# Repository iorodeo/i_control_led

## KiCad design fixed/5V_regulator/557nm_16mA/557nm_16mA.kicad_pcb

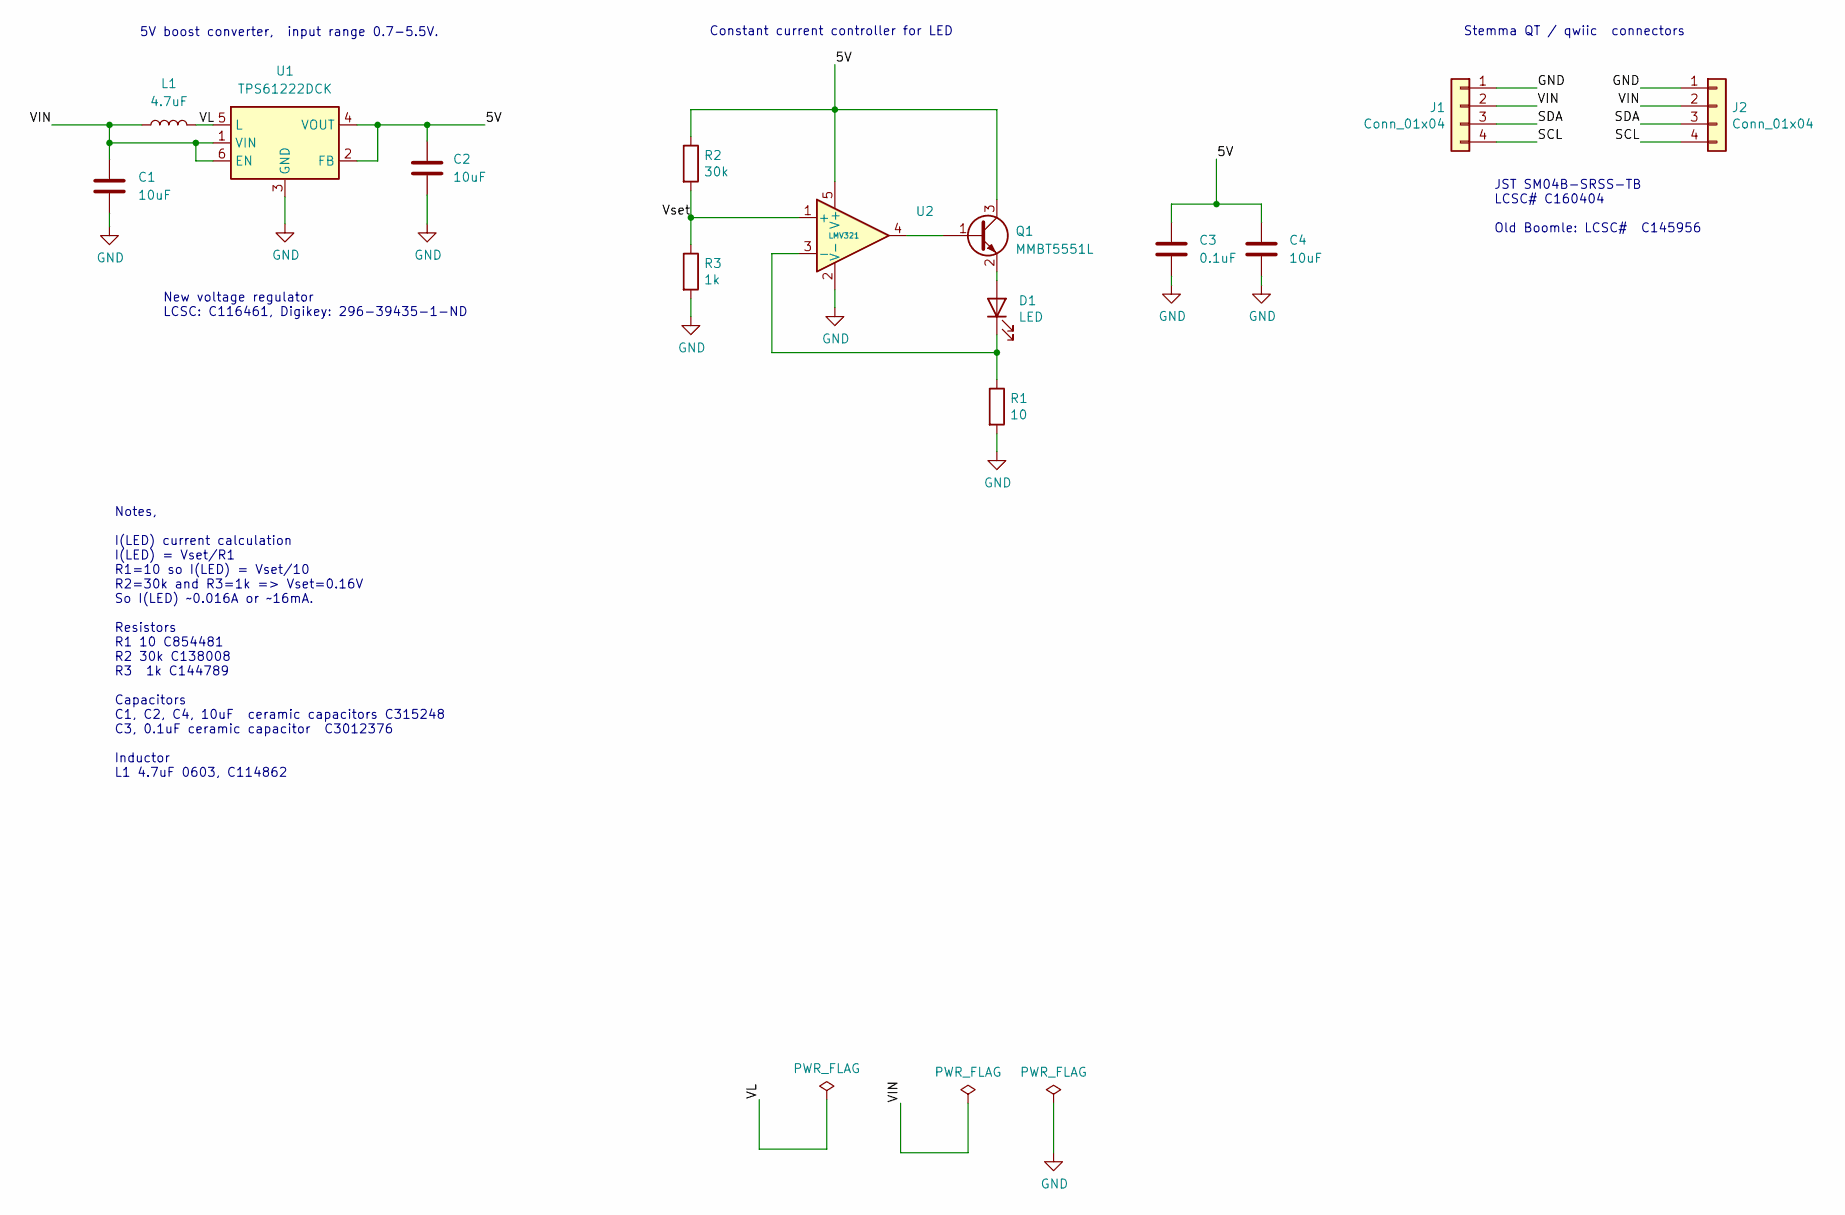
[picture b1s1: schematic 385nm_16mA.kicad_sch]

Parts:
C1, C2, C4: 10uF; C_0402_1005Metric
C3: 0.1uF; C_0402_1005Metric
D1: LED; LED_0805_2012Metric
J1, J2: Conn_01x04; JST_SH_SM04B-SRSS-TB_1x04-1MP_P1.00mm_Horizontal
L1: 4.7uF; L_0603_1608Metric
Q1: MMBT5551L; SOT-23
R1: 10; R_0402_1005Metric
R2: 30k; R_0402_1005Metric
R3: 1k; R_0402_1005Metric
U1: TPS61222DCK; SOT-363_SC-70-6
U2: LMV321; SOT-23-5

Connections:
/5V: C2.2, C3.1, C4.1, Q1.3 (C), R2.1, U1.2 (FB), U1.4 (VOUT), U2.5 (V+)
/SCL: J1.4, J2.4
/SDA: J1.3, J2.3
/VIN: C1.2, J1.2, J2.2, L1.1, U1.1 (VIN), U1.6 (EN)
/VL: L1.2, U1.5 (L)
/Vset: R2.2, R3.1, U2.1 (+)
GND: C1.1, C2.1, C3.2, C4.2, J1.1, J2.1, R1.2, R3.2, U1.3 (GND), U2.2 (V-)
unnamed: D1.2 (A), Q1.2 (E)
unnamed: D1.1 (K), R1.1, U2.3 (-)
unnamed: Q1.1 (B), U2.4

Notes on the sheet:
JST SM04B-SRSS-TB LCSC# C160404 Old Boomle: LCSC# C145956
Stemma QT / qwiic connectors
New voltage regulator LCSC: C116461, Digikey: 296-39435-1-ND
Constant current controller for LED
5V boost converter, input range 0.7-5.5V.
Notes, I(LED) current calculation I(LED) = Vset/R1 R1=10 so I(LED) = Vset/10 R2=30k and R3=1k => Vset=0.16V So I(LED) ~0.016A or ~16mA. Resistors R1 10 C854481 R2 30k C138008 R3 1k C144789 Capacitors C1, C2, C4, 10uF ceramic capacitors C315248 C3, 0.1uF ceramic capacitor C3012376 Inductor L1 4.7uF 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

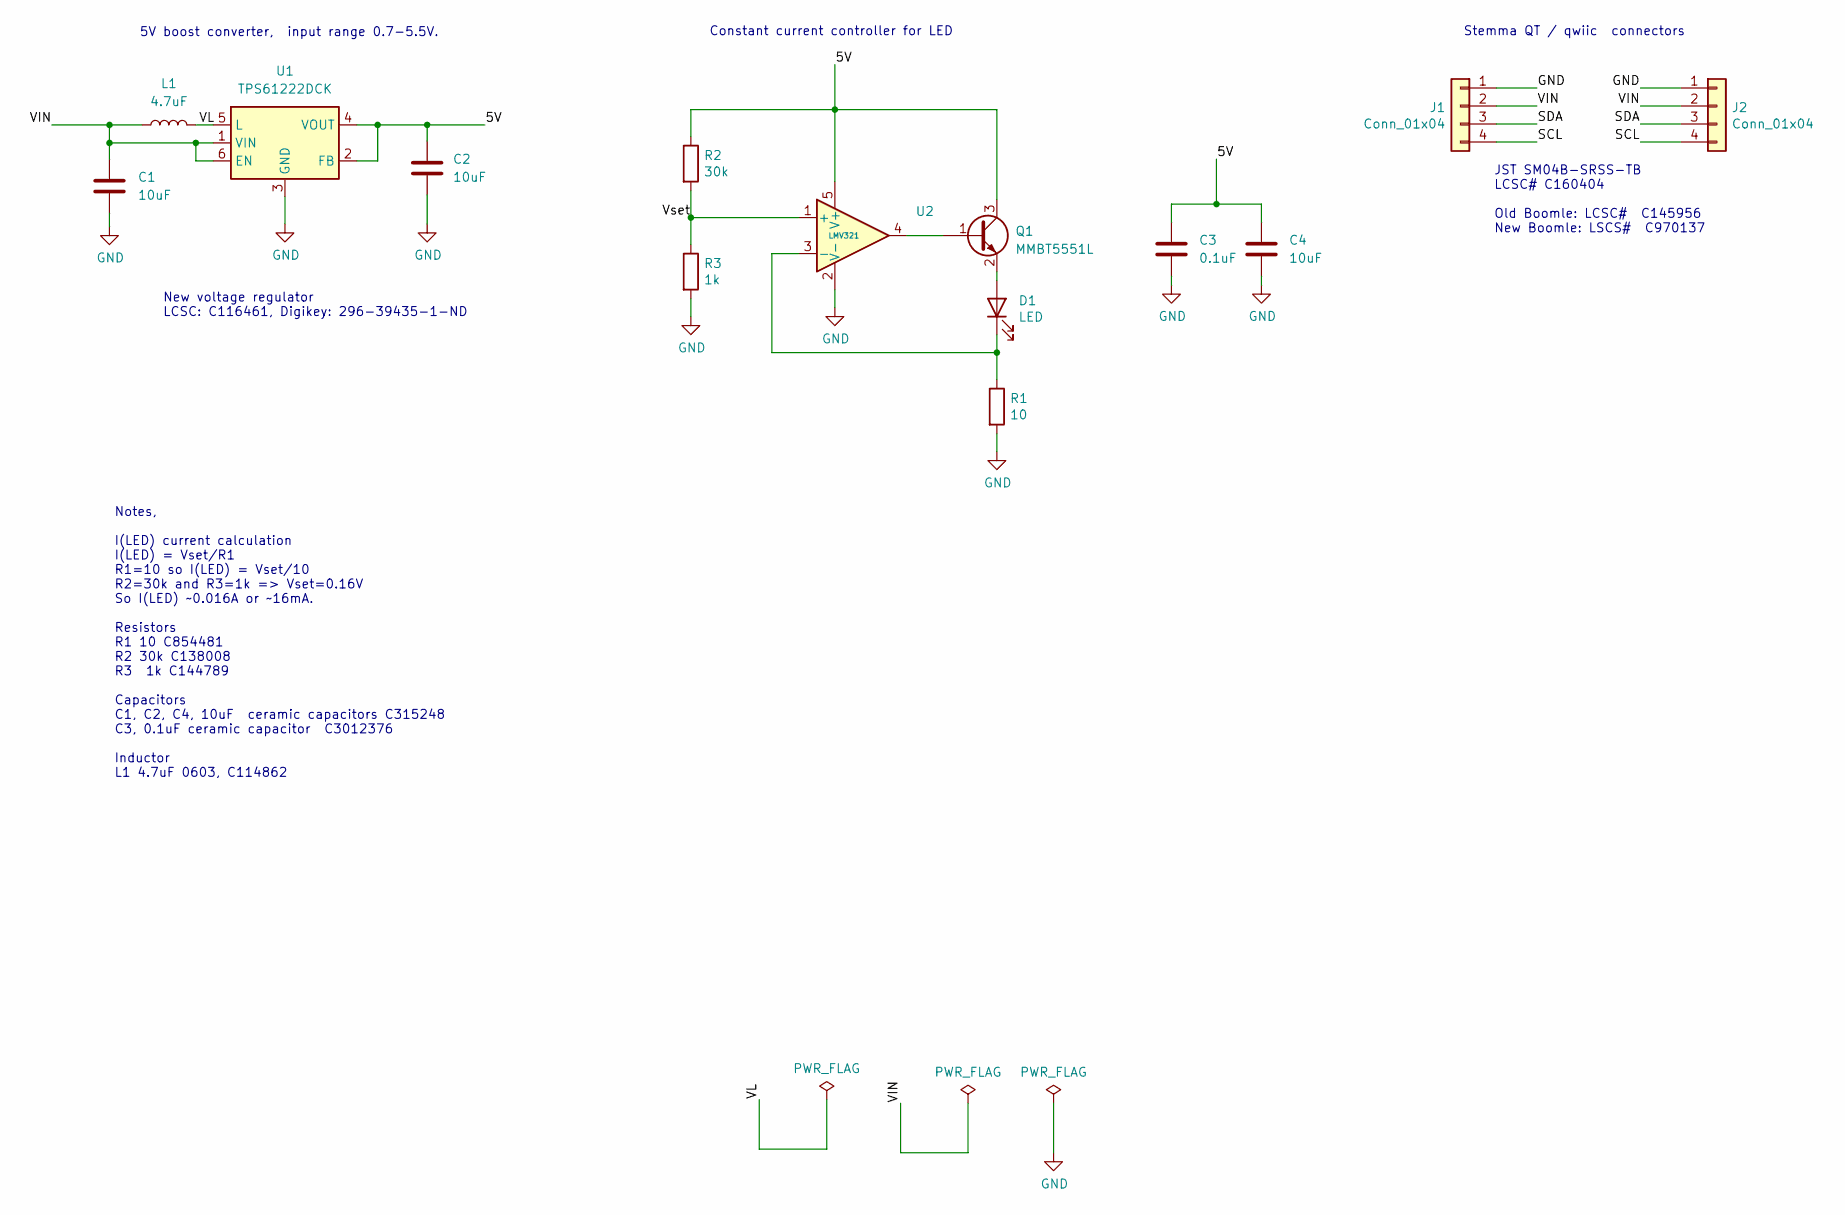
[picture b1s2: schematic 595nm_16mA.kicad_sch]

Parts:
C1, C2, C4: 10uF; C_0402_1005Metric
C3: 0.1uF; C_0402_1005Metric
D1: LED; LED_0603_1608Metric
J1, J2: Conn_01x04; JST_SH_SM04B-SRSS-TB_1x04-1MP_P1.00mm_Horizontal
L1: 4.7uF; L_0603_1608Metric
Q1: MMBT5551L; SOT-23
R1: 10; R_0402_1005Metric
R2: 30k; R_0402_1005Metric
R3: 1k; R_0402_1005Metric
U1: TPS61222DCK; SOT-363_SC-70-6
U2: LMV321; SOT-23-5

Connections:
/5V: C2.2, C3.1, C4.1, Q1.3 (C), R2.1, U1.2 (FB), U1.4 (VOUT), U2.5 (V+)
/SCL: J1.4, J2.4
/SDA: J1.3, J2.3
/VIN: C1.2, J1.2, J2.2, L1.1, U1.1 (VIN), U1.6 (EN)
/VL: L1.2, U1.5 (L)
/Vset: R2.2, R3.1, U2.1 (+)
GND: C1.1, C2.1, C3.2, C4.2, J1.1, J2.1, R1.2, R3.2, U1.3 (GND), U2.2 (V-)
unnamed: D1.2 (A), Q1.2 (E)
unnamed: D1.1 (K), R1.1, U2.3 (-)
unnamed: Q1.1 (B), U2.4

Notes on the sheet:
JST SM04B-SRSS-TB LCSC# C160404 Old Boomle: LCSC# C145956 New Boomle: LSCS# C970137
Stemma QT / qwiic connectors
New voltage regulator LCSC: C116461, Digikey: 296-39435-1-ND
Constant current controller for LED
5V boost converter, input range 0.7-5.5V.
Notes, I(LED) current calculation I(LED) = Vset/R1 R1=10 so I(LED) = Vset/10 R2=30k and R3=1k => Vset=0.16V So I(LED) ~0.016A or ~16mA. Resistors R1 10 C854481 R2 30k C138008 R3 1k C144789 Capacitors C1, C2, C4, 10uF ceramic capacitors C315248 C3, 0.1uF ceramic capacitor C3012376 Inductor L1 4.7uF 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

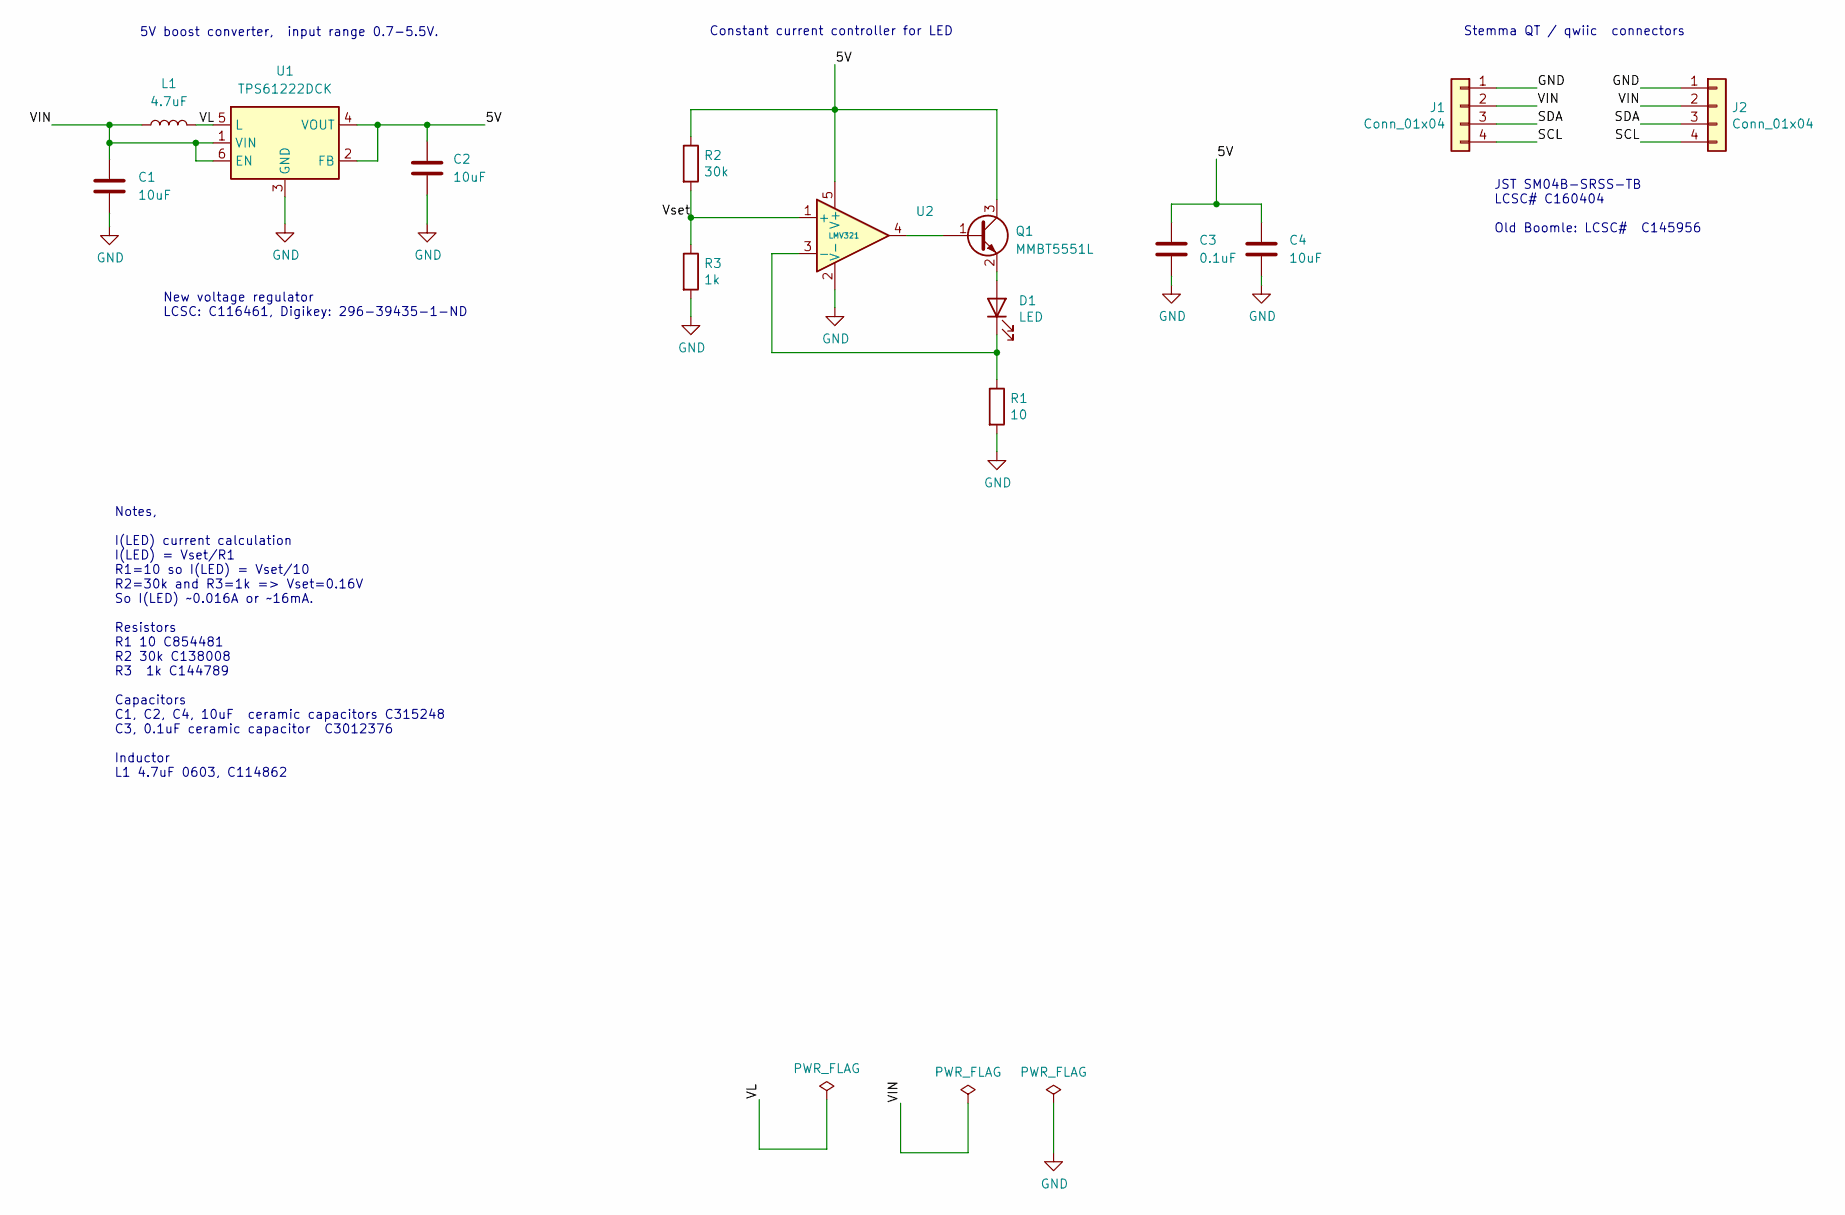
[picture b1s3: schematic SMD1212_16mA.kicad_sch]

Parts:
C1, C2, C4: 10uF; C_0402_1005Metric
C3: 0.1uF; C_0402_1005Metric
D1: LED; SMD1212
J1, J2: Conn_01x04; JST_SH_SM04B-SRSS-TB_1x04-1MP_P1.00mm_Horizontal
L1: 4.7uF; L_0603_1608Metric
Q1: MMBT5551L; SOT-23
R1: 10; R_0402_1005Metric
R2: 30k; R_0402_1005Metric
R3: 1k; R_0402_1005Metric
U1: TPS61222DCK; SOT-363_SC-70-6
U2: LMV321; SOT-23-5

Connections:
/5V: C2.2, C3.1, C4.1, Q1.3 (C), R2.1, U1.2 (FB), U1.4 (VOUT), U2.5 (V+)
/SCL: J1.4, J2.4
/SDA: J1.3, J2.3
/VIN: C1.2, J1.2, J2.2, L1.1, U1.1 (VIN), U1.6 (EN)
/VL: L1.2, U1.5 (L)
/Vset: R2.2, R3.1, U2.1 (+)
GND: C1.1, C2.1, C3.2, C4.2, J1.1, J2.1, R1.2, R3.2, U1.3 (GND), U2.2 (V-)
unnamed: D1.2 (A), Q1.2 (E)
unnamed: D1.1 (K), R1.1, U2.3 (-)
unnamed: Q1.1 (B), U2.4

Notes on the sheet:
JST SM04B-SRSS-TB LCSC# C160404 Old Boomle: LCSC# C145956
Stemma QT / qwiic connectors
New voltage regulator LCSC: C116461, Digikey: 296-39435-1-ND
Constant current controller for LED
5V boost converter, input range 0.7-5.5V.
Notes, I(LED) current calculation I(LED) = Vset/R1 R1=10 so I(LED) = Vset/10 R2=30k and R3=1k => Vset=0.16V So I(LED) ~0.016A or ~16mA. Resistors R1 10 C854481 R2 30k C138008 R3 1k C144789 Capacitors C1, C2, C4, 10uF ceramic capacitors C315248 C3, 0.1uF ceramic capacitor C3012376 Inductor L1 4.7uF 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

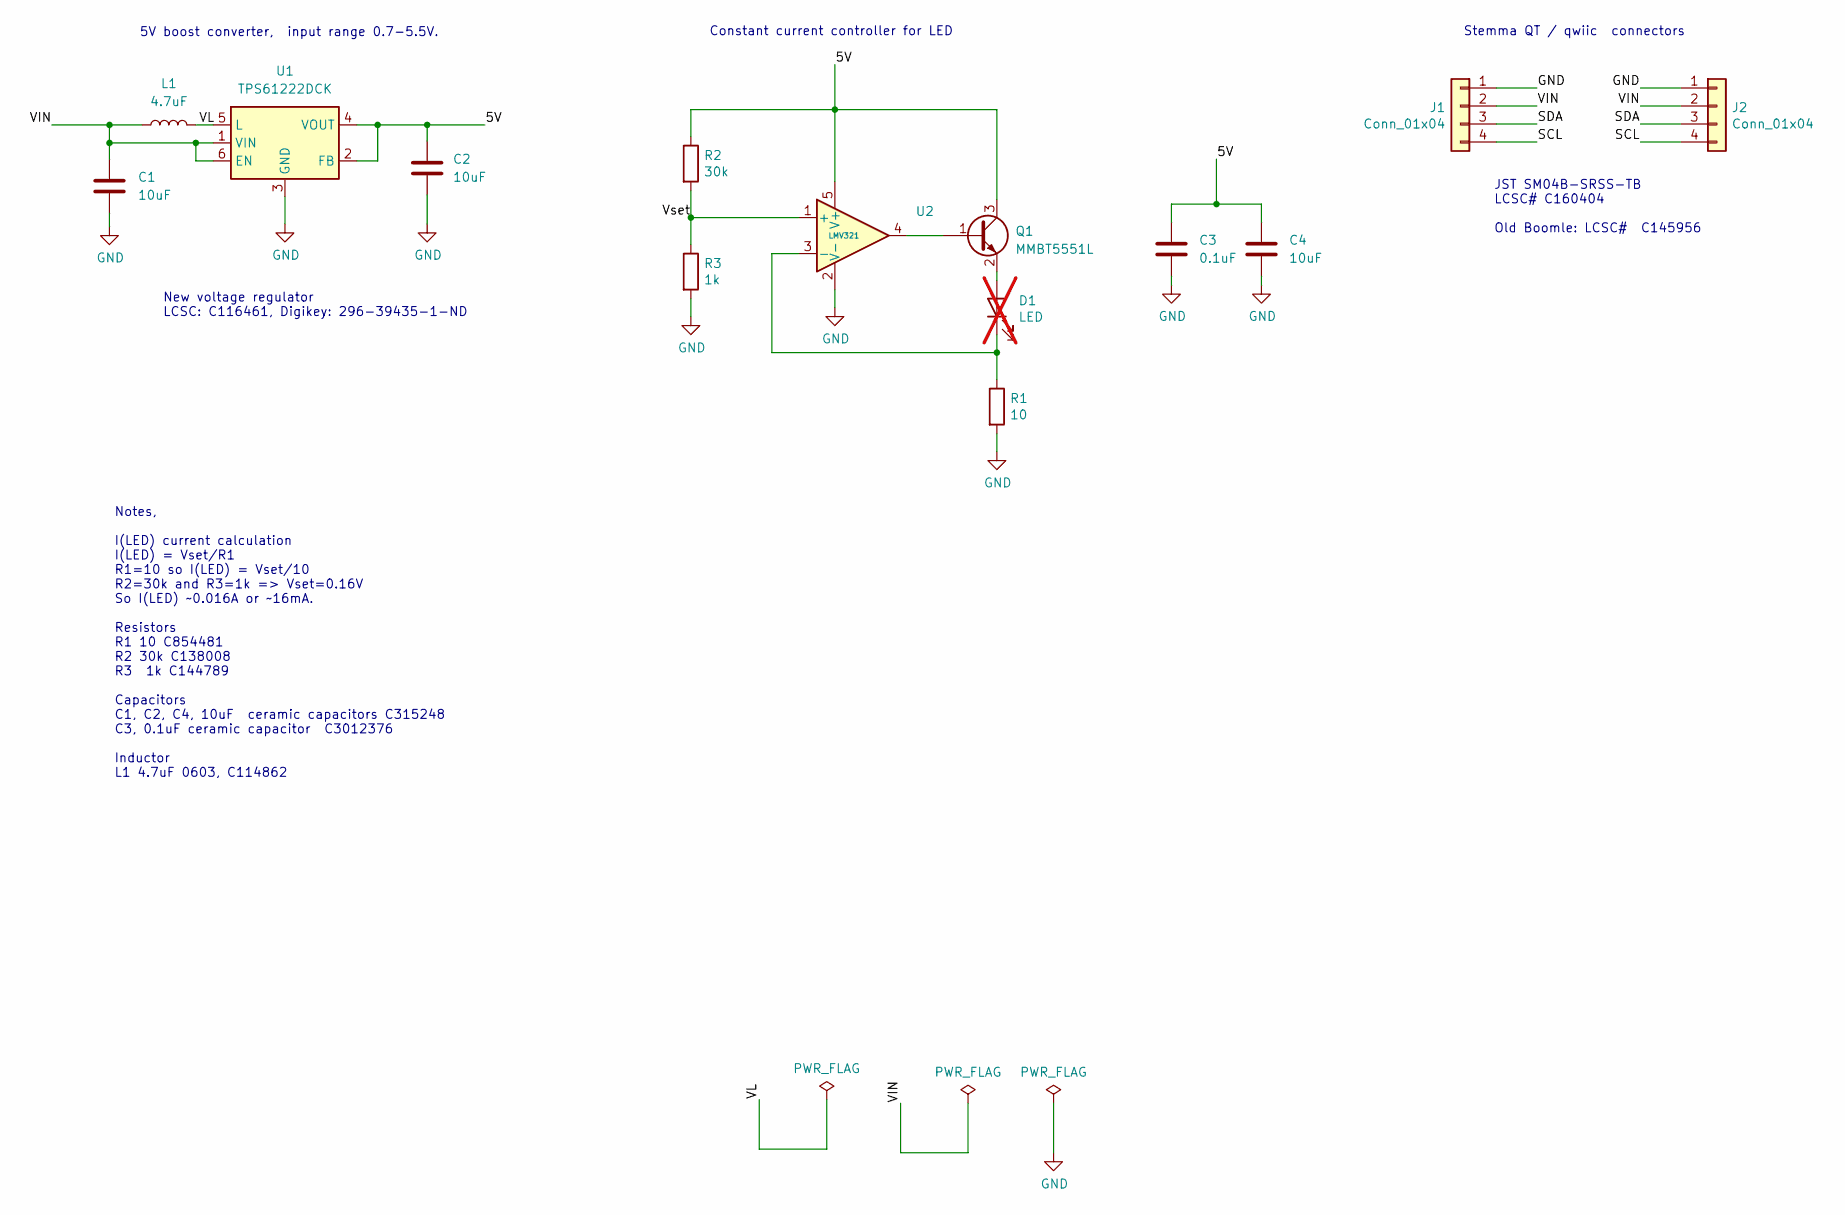
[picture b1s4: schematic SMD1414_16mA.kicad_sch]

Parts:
C1, C2, C4: 10uF; C_0402_1005Metric; LCSC Part # C315248
C3: 0.1uF; C_0402_1005Metric; LCSC Part # C1525
D1: LED; LED_1414; not fitted
J1, J2: Conn_01x04; JST_SH_SM04B-SRSS-TB_1x04-1MP_P1.00mm_Horizontal; LCSC Part # C160404
L1: 4.7uF; L_0603_1608Metric; LCSC Part # C114862
Q1: MMBT5551L; SOT-23; LCSC Part # C41095
R1: 10; R_0402_1005Metric; LCSC Part # C413044
R2: 30k; R_0402_1005Metric; LCSC Part # C138008
R3: 1k; R_0402_1005Metric; LCSC Part # C144789
U1: TPS61222DCK; SOT-363_SC-70-6; LCSC Part # C116461
U2: LMV321; SOT-23-5; LCSC Part # C7972

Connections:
/5V: C2.2, C3.1, C4.1, Q1.3 (C), R2.1, U1.2 (FB), U1.4 (VOUT), U2.5 (V+)
/SCL: J1.4, J2.4
/SDA: J1.3, J2.3
/VIN: C1.2, J1.2, J2.2, L1.1, U1.1 (VIN), U1.6 (EN)
/VL: L1.2, U1.5 (L)
/Vset: R2.2, R3.1, U2.1 (+)
GND: C1.1, C2.1, C3.2, C4.2, J1.1, J2.1, R1.2, R3.2, U1.3 (GND), U2.2 (V-)
unnamed: D1.2 (A), Q1.2 (E)
unnamed: D1.1 (K), R1.1, U2.3 (-)
unnamed: Q1.1 (B), U2.4

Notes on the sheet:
JST SM04B-SRSS-TB LCSC# C160404 Old Boomle: LCSC# C145956
Stemma QT / qwiic connectors
New voltage regulator LCSC: C116461, Digikey: 296-39435-1-ND
Constant current controller for LED
5V boost converter, input range 0.7-5.5V.
Notes, I(LED) current calculation I(LED) = Vset/R1 R1=10 so I(LED) = Vset/10 R2=30k and R3=1k => Vset=0.16V So I(LED) ~0.016A or ~16mA. Resistors R1 10 C854481 R2 30k C138008 R3 1k C144789 Capacitors C1, C2, C4, 10uF ceramic capacitors C315248 C3, 0.1uF ceramic capacitor C3012376 Inductor L1 4.7uF 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

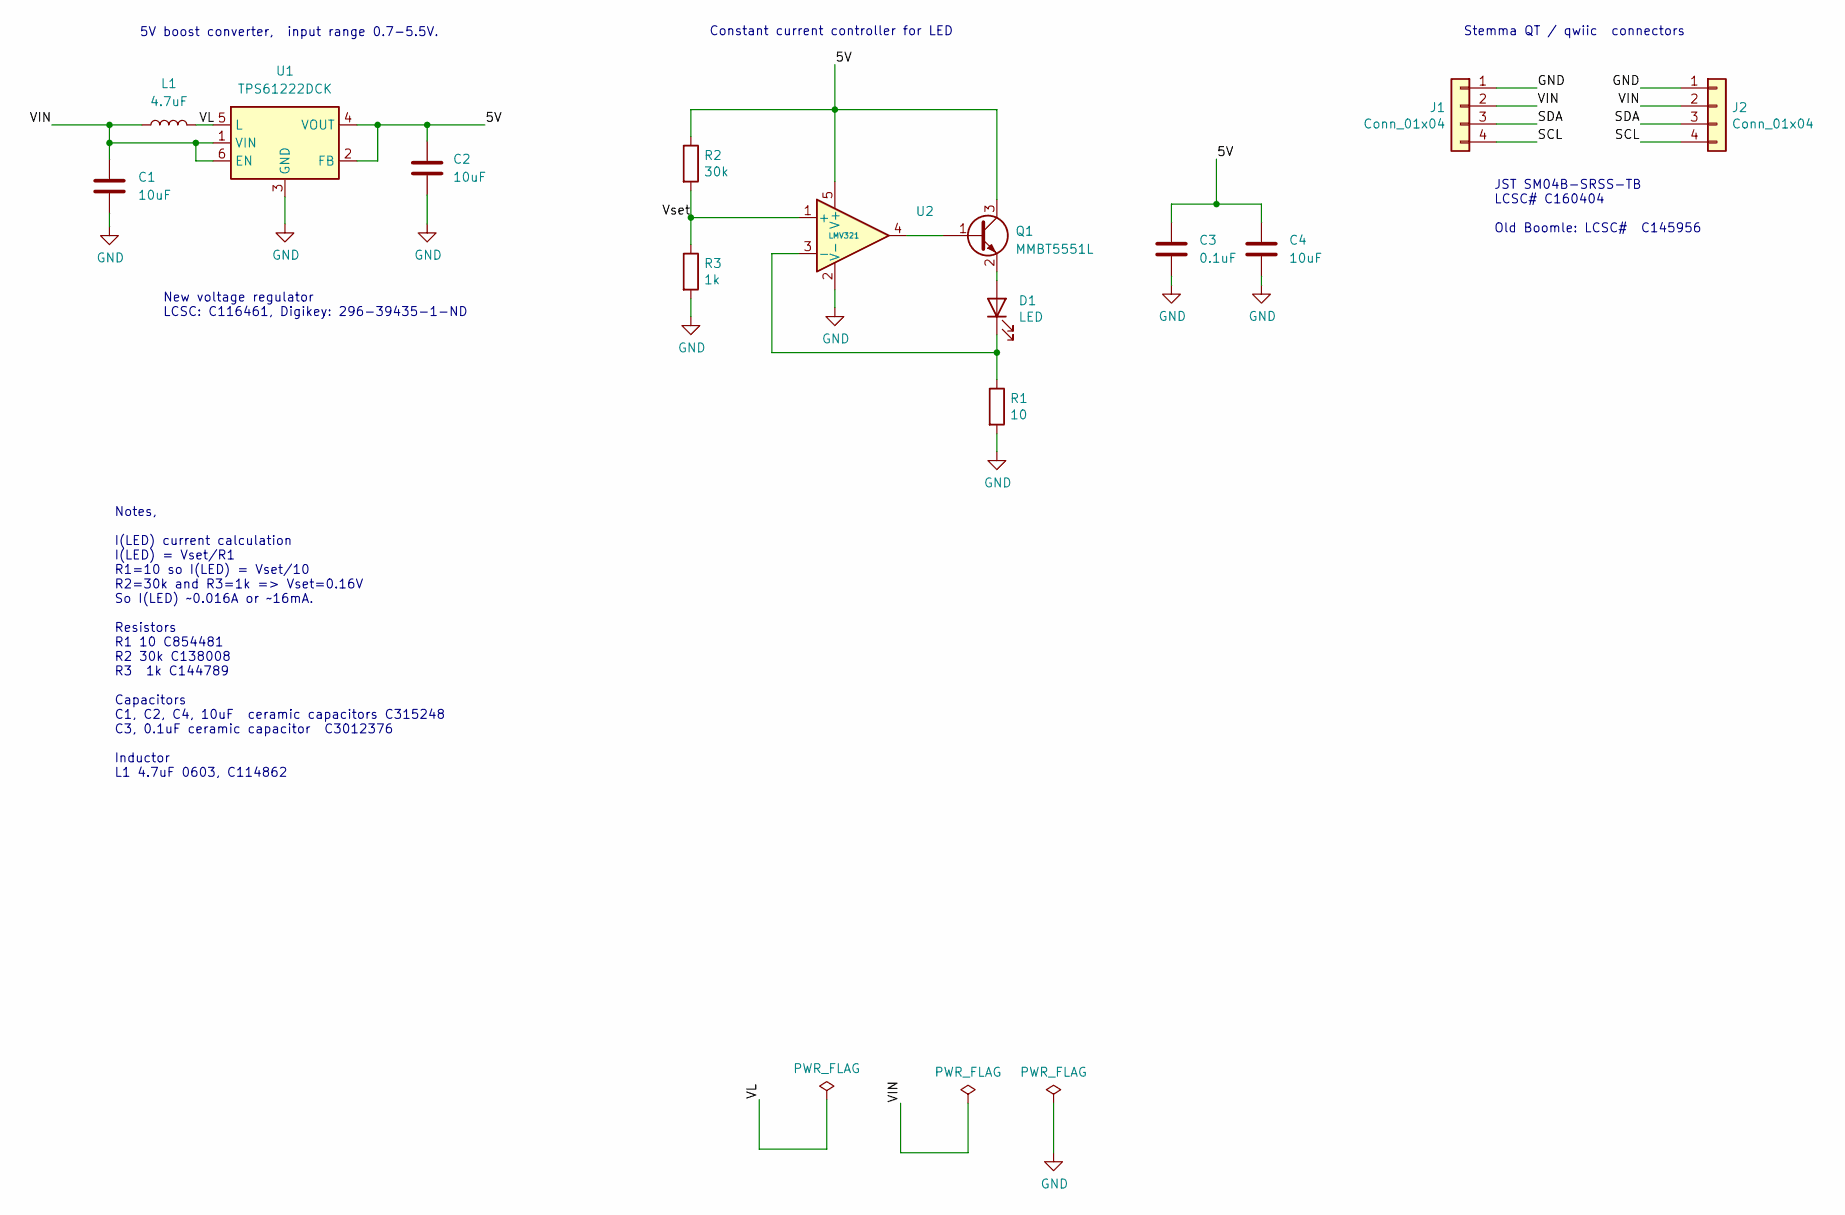
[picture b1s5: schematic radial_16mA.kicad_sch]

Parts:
C1, C2, C4: 10uF; C_0402_1005Metric
C3: 0.1uF; C_0402_1005Metric
D1: LED; LED_D3.0mm
J1, J2: Conn_01x04; JST_SH_SM04B-SRSS-TB_1x04-1MP_P1.00mm_Horizontal
L1: 4.7uF; L_0603_1608Metric
Q1: MMBT5551L; SOT-23
R1: 10; R_0402_1005Metric
R2: 30k; R_0402_1005Metric
R3: 1k; R_0402_1005Metric
U1: TPS61222DCK; SOT-363_SC-70-6
U2: LMV321; SOT-23-5

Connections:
/5V: C2.2, C3.1, C4.1, Q1.3 (C), R2.1, U1.2 (FB), U1.4 (VOUT), U2.5 (V+)
/SCL: J1.4, J2.4
/SDA: J1.3, J2.3
/VIN: C1.2, J1.2, J2.2, L1.1, U1.1 (VIN), U1.6 (EN)
/VL: L1.2, U1.5 (L)
/Vset: R2.2, R3.1, U2.1 (+)
GND: C1.1, C2.1, C3.2, C4.2, J1.1, J2.1, R1.2, R3.2, U1.3 (GND), U2.2 (V-)
unnamed: D1.2 (A), Q1.2 (E)
unnamed: D1.1 (K), R1.1, U2.3 (-)
unnamed: Q1.1 (B), U2.4

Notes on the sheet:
JST SM04B-SRSS-TB LCSC# C160404 Old Boomle: LCSC# C145956
Stemma QT / qwiic connectors
New voltage regulator LCSC: C116461, Digikey: 296-39435-1-ND
Constant current controller for LED
5V boost converter, input range 0.7-5.5V.
Notes, I(LED) current calculation I(LED) = Vset/R1 R1=10 so I(LED) = Vset/10 R2=30k and R3=1k => Vset=0.16V So I(LED) ~0.016A or ~16mA. Resistors R1 10 C854481 R2 30k C138008 R3 1k C144789 Capacitors C1, C2, C4, 10uF ceramic capacitors C315248 C3, 0.1uF ceramic capacitor C3012376 Inductor L1 4.7uF 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

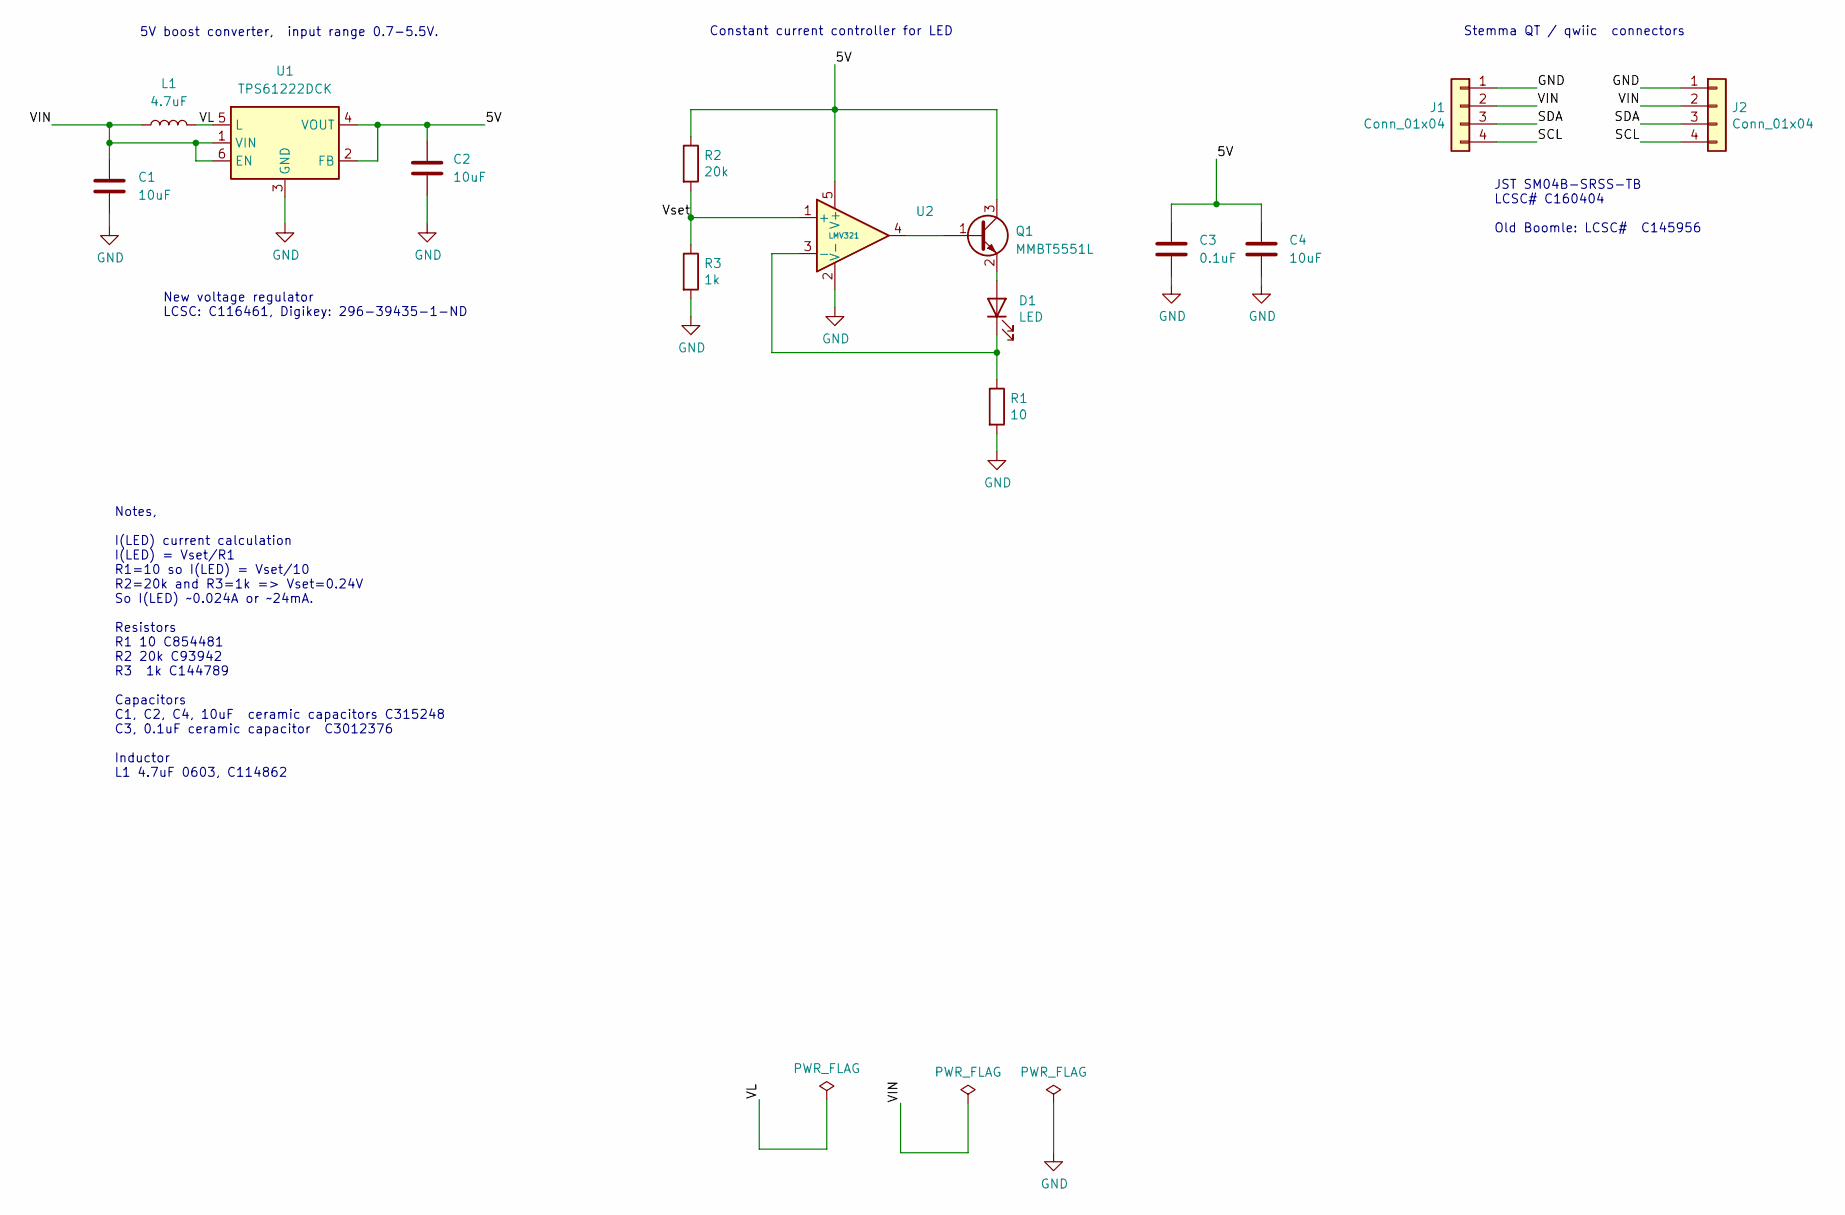
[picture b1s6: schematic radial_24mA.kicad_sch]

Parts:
C1, C2, C4: 10uF; C_0402_1005Metric
C3: 0.1uF; C_0402_1005Metric
D1: LED; LED_D3.0mm
J1, J2: Conn_01x04; JST_SH_SM04B-SRSS-TB_1x04-1MP_P1.00mm_Horizontal
L1: 4.7uF; L_0603_1608Metric
Q1: MMBT5551L; SOT-23
R1: 10; R_0402_1005Metric
R2: 20k; R_0402_1005Metric
R3: 1k; R_0402_1005Metric
U1: TPS61222DCK; SOT-363_SC-70-6
U2: LMV321; SOT-23-5

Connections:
/5V: C2.2, C3.1, C4.1, Q1.3 (C), R2.1, U1.2 (FB), U1.4 (VOUT), U2.5 (V+)
/SCL: J1.4, J2.4
/SDA: J1.3, J2.3
/VIN: C1.2, J1.2, J2.2, L1.1, U1.1 (VIN), U1.6 (EN)
/VL: L1.2, U1.5 (L)
/Vset: R2.2, R3.1, U2.1 (+)
GND: C1.1, C2.1, C3.2, C4.2, J1.1, J2.1, R1.2, R3.2, U1.3 (GND), U2.2 (V-)
unnamed: D1.2 (A), Q1.2 (E)
unnamed: D1.1 (K), R1.1, U2.3 (-)
unnamed: Q1.1 (B), U2.4

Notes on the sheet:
JST SM04B-SRSS-TB LCSC# C160404 Old Boomle: LCSC# C145956
Stemma QT / qwiic connectors
New voltage regulator LCSC: C116461, Digikey: 296-39435-1-ND
Constant current controller for LED
5V boost converter, input range 0.7-5.5V.
Notes, I(LED) current calculation I(LED) = Vset/R1 R1=10 so I(LED) = Vset/10 R2=20k and R3=1k => Vset=0.24V So I(LED) ~0.024A or ~24mA. Resistors R1 10 C854481 R2 20k C93942 R3 1k C144789 Capacitors C1, C2, C4, 10uF ceramic capacitors C315248 C3, 0.1uF ceramic capacitor C3012376 Inductor L1 4.7uF 0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

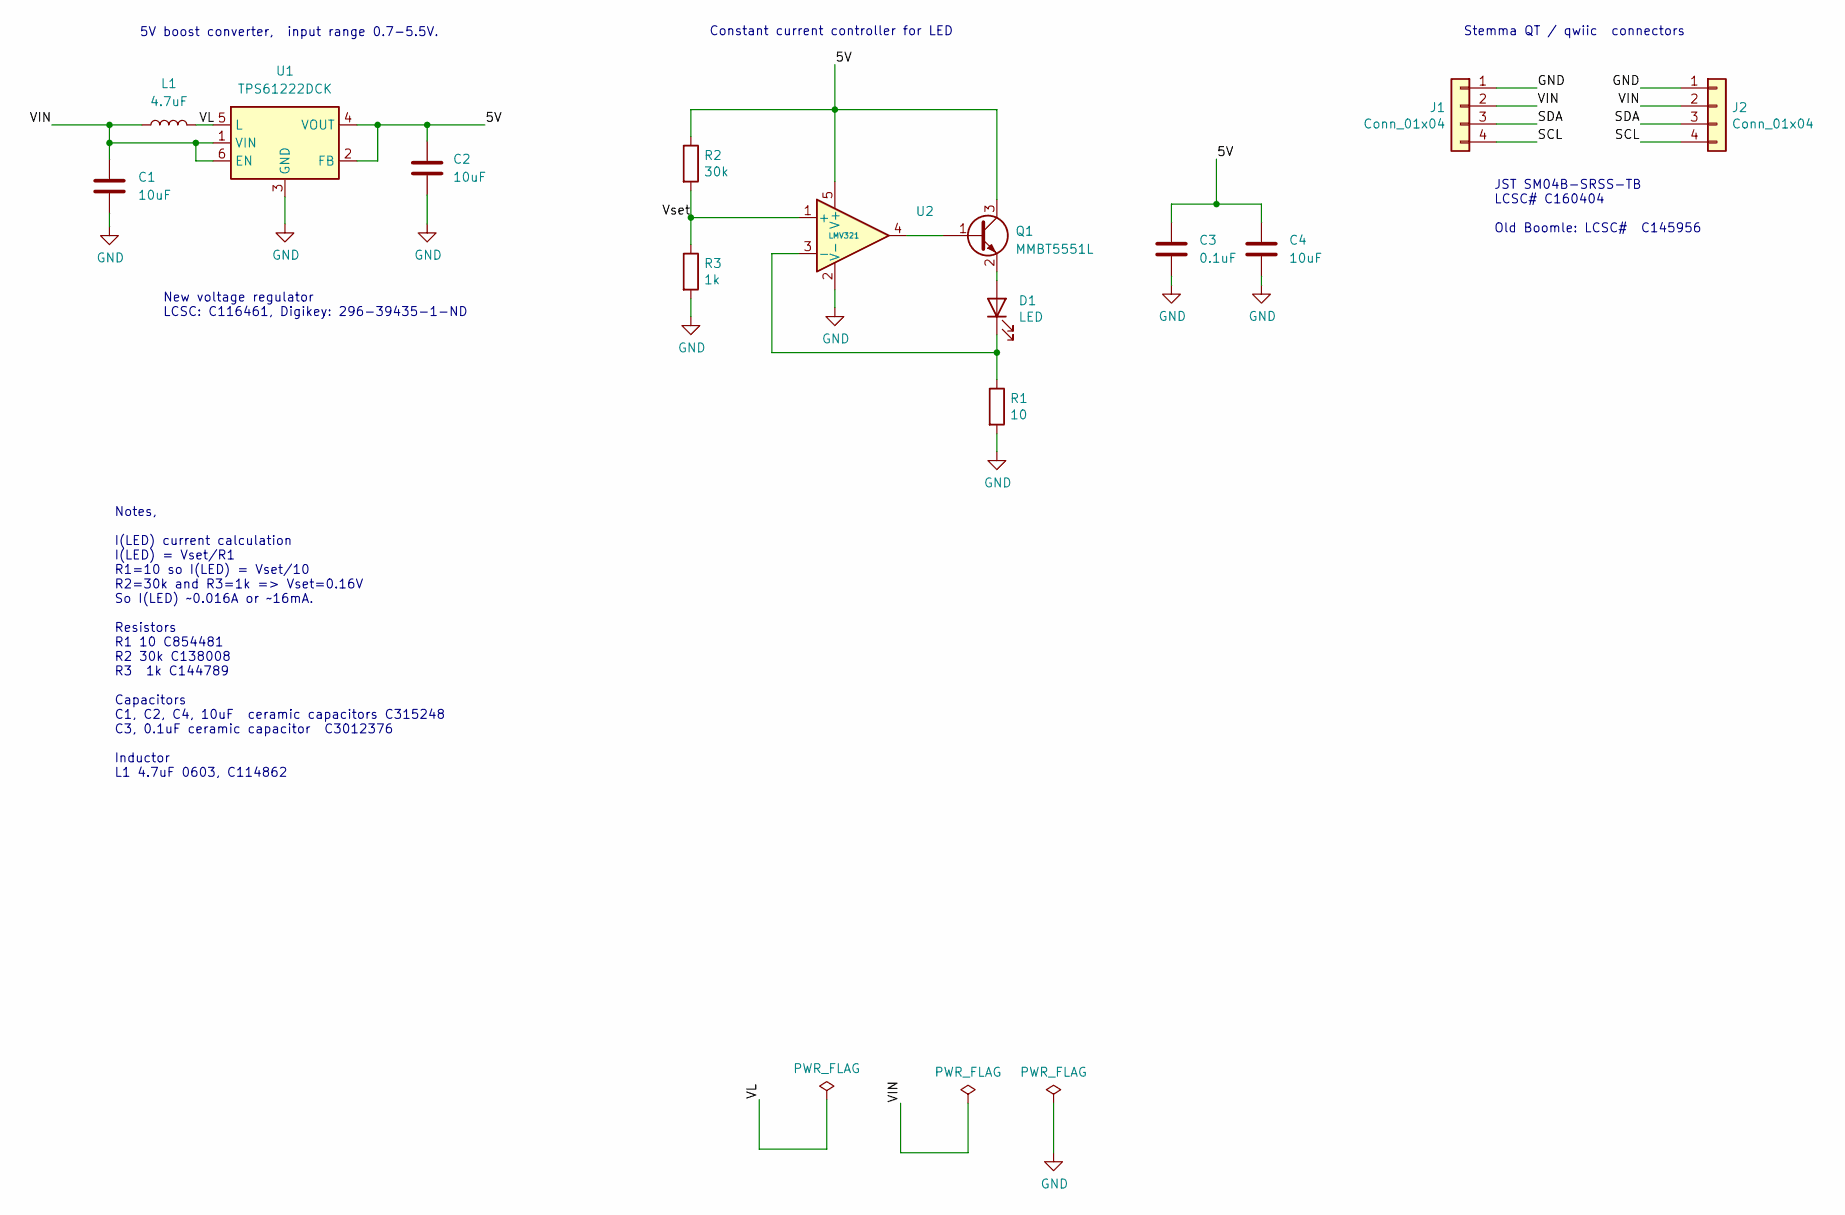
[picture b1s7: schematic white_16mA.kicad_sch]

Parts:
C1, C2, C4: 10uF; C_0402_1005Metric
C3: 0.1uF; C_0402_1005Metric
D1: LED; LED_0603_1608Metric
J1, J2: Conn_01x04; JST_SH_SM04B-SRSS-TB_1x04-1MP_P1.00mm_Horizontal
L1: 4.7uF; L_0603_1608Metric
Q1: MMBT5551L; SOT-23
R1: 10; R_0402_1005Metric
R2: 30k; R_0402_1005Metric
R3: 1k; R_0402_1005Metric
U1: TPS61222DCK; SOT-363_SC-70-6
U2: LMV321; SOT-23-5

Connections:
/5V: C2.2, C3.1, C4.1, Q1.3 (C), R2.1, U1.2 (FB), U1.4 (VOUT), U2.5 (V+)
/SCL: J1.4, J2.4
/SDA: J1.3, J2.3
/VIN: C1.2, J1.2, J2.2, L1.1, U1.1 (VIN), U1.6 (EN)
/VL: L1.2, U1.5 (L)
/Vset: R2.2, R3.1, U2.1 (+)
GND: C1.1, C2.1, C3.2, C4.2, J1.1, J2.1, R1.2, R3.2, U1.3 (GND), U2.2 (V-)
unnamed: D1.2 (A), Q1.2 (E)
unnamed: D1.1 (K), R1.1, U2.3 (-)
unnamed: Q1.1 (B), U2.4

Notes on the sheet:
JST SM04B-SRSS-TB LCSC# C160404 Old Boomle: LCSC# C145956
Stemma QT / qwiic connectors
New voltage regulator LCSC: C116461, Digikey: 296-39435-1-ND
Constant current controller for LED
5V boost converter, input range 0.7-5.5V.
Notes, I(LED) current calculation I(LED) = Vset/R1 R1=10 so I(LED) = Vset/10 R2=30k and R3=1k => Vset=0.16V So I(LED) ~0.016A or ~16mA. Resistors R1 10 C854481 R2 30k C138008 R3 1k C144789 Capacitors C1, C2, C4, 10uF ceramic capacitors C315248 C3, 0.1uF ceramic capacitor C3012376 Inductor L1 4.7uF 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
